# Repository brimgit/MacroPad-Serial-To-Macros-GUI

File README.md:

# MacroPad

A full-featured desktop app for controlling a custom ESP32-based macropad over serial. Built with a **React + Vite** frontend running inside a **pywebview** frameless window, backed by a pure-Python layer for serial communication, audio control, and macro execution.

---

## Features

### Macros
- Assign **press** and **hold** actions to all 8 keys and 4 encoder buttons
- **Configurable hold duration** per key (100–3000 ms, default 500 ms)
- **Drag keys to swap** their assignments directly on the grid
- **Copy / Paste** macros between keys with one click
- **Undo** the last macro edit with a single button
- Supported macro types:

  | Type | Description |
  |---|---|
  | Keyboard Key | Any letter, number, or special key |
  | Media Control | Play/pause, next/prev track, volume up/down, mute |
  | Function Key | F1–F24 |
  | Modifier Key | Ctrl, Shift, Alt, Win, and combos (Ctrl+C, Alt+Tab, etc.) |
  | Type Text | Types a free-form string |
  | Launch | Opens a file, folder, application, or URL |
  | System | Lock screen, sleep, shutdown, or restart |
  | Mute App | Toggles mute for the encoder's assigned audio source |
  | Recorded | Records a full keyboard sequence and replays it with original timing |
  | Multi Action | Chains multiple macro steps into a single key press |

### Encoders
- Each of the 4 encoders independently controls a volume source:
  - **Any audio app** (Discord, Spotify, browsers, games, etc.)
  - **🔊 Master Volume** — system-wide output level
  - **🎤 Microphone** — default capture device input level
- Each app can only be assigned to **one encoder at a time** — assigning it elsewhere automatically clears the previous one
- **Offline indicator** — encoder card shows a yellow **● OFFLINE** badge if the assigned app is not currently running
- Encoder **button macros** (press + hold) assignable per encoder, same types as keys
- **Mute toggle**: pressing the encoder button mutes/unmutes the source
  - LED ring turns **solid red** while muted
  - Turning while muted **flashes red continuously**, then gives 3 final blinks to confirm still muted
  - Mute state is **read on connect** so the ring reflects reality immediately

### LED Ring
Each encoder card shows a live **10-LED ring preview** that mirrors the physical device:
- **Volume display** — LEDs fill proportional to current volume %, shown for 2 s after each turn
- **Idle animations**:

  | Effect | Description |
  |---|---|
  | Off | Strip turns off after timeout |
  | Breathe | All LEDs pulse in and out (smootherstep curve) |
  | Wave | Brightness ripples across the ring |
  | Rainbow | Hue band scrolls around the ring |
  | Chase | Bright spot bounces with fade trail |
  | Color Cycle | All LEDs drift through the full spectrum |
  | Sparkle | Random LEDs flash in the encoder's color |

- **LED modes** (color while active):
  - **Default** — green→red gradient tracking volume
  - **Solid** — single custom color
  - **Fade** — gradient between two custom colors

### Profiles
- **Create, rename, duplicate, and delete** named profiles
- Each profile stores: all key macros, encoder button macros, encoder app assignments, LED mode/colors/effects
- **Import / Export** profiles as `.json` files
- Profiles are stored as **individual files** (`Data/profiles/{name}.json`) — easy to back up, diff, and share
- **Auto profile switching** — configure a list of trigger apps per profile; the active profile switches automatically when that app comes into focus

### Settings
| Setting | Description |
|---|---|
| Serial Port & Baud Rate | Connect to the MacroPad over any COM port |
| LED Brightness | Global brightness (0–100%) sent to device on change |
| Enc LED Off | Idle timeout before encoder strip turns off (2 / 5 / 10 s) |
| Effect Speed | Animation frame rate: 5 ms (Ultra) → 50 ms (Light) |
| Export / Import Profile | Save or load the active profile as a `.json` file |
| Start with Windows | Adds MacroPad to the Windows startup registry key |

### Other
- **Device auto-detection** — on startup the app sends a `PING` to the configured port and looks for `MACROPAD_OK`; if the wrong port is saved it scans all available ports automatically and updates the setting
- **Frameless window** with a custom title bar — minimize, maximize, and close buttons blend into the app's colour scheme; the bar is draggable
- **Collapsible sidebar** — collapse to icon-only mode to save screen space; hover tooltips identify each page
- **Auto-reconnect** — if the device is unplugged the app reconnects automatically and restores all LED state
- **Test Mode** — shows all 8 key assignments with live flash highlighting and a scrolling event log when keys are pressed
- **Firmware Upload** — compile and flash `.ino` sketches directly from the app via Arduino CLI with a live log output
- **Update checker** — checks GitHub for a newer version on the Settings page

---

## Hardware

PCB designed in **KiCad** — schematic, board files, and Gerber files are in `PCB_files/`. Order directly from any PCB manufacturer with the Gerbers.

**ESP32** microcontroller with:
- 4× rotary encoders with push button (A/B/C/D)
- 8× mechanical keys (1–8)
- 4× NeoPixel LED strips (10 LEDs each, surrounding each encoder knob)

---

## Running from Source

### Requirements
- Python 3.10+
- Node.js 18+ (for building the frontend)

### Install dependencies

```bash
git clone https://github.com/brimgit/MacroPad-Serial-To-Macros-GUI
cd MacroPad-Serial-To-Macros-GUI

# Python dependencies
pip install -r requirements.txt

# Frontend dependencies
cd frontend
npm install
cd ..
```

### Development mode (hot-reload)

```bash
# Terminal 1 — Vite dev server
cd frontend
npm run dev

# Terminal 2 — Python backend (connects to Vite at localhost:5173)
python src/main_webview.py --dev
```

### Production mode (no Node.js needed at runtime)

```bash
# Build the frontend once
cd frontend
npm run build
cd ..

# Run the app
python src/main_webview.py
```

### Python dependencies

| Package | Purpose |
|---|---|
| pywebview | Native frameless window hosting the React frontend |
| pyserial | Serial communication with ESP32 |
| keyboard | Macro execution and keystroke recording |
| pycaw | Windows audio session / endpoint volume control |
| psutil | Process name lookup for auto profile switching |

### Frontend stack

| Package | Purpose |
|---|---|
| React 19 | UI framework |
| Vite | Build tool and dev server |

---

## Project Structure

```
src/
  main_webview.py      # Entry point — creates frameless pywebview window
  api.py               # Python API exposed to React via pywebview JS bridge
  macro_manager.py     # Macro storage, persistence, and execution
  profile_manager.py   # Profile CRUD, per-file JSON persistence
  serial_manager.py    # Serial connection, device identification, auto-reconnect
  volume_manager.py    # Per-app, master, and microphone volume control (pycaw)
  foreground_watcher.py# Polls foreground window for auto profile switching
  utils.py             # Path helpers for PyInstaller and data directory

frontend/
  src/
    App.jsx                     # Root component, state, event listeners
    components/
      Sidebar.jsx               # Navigation, profile management, theme toggle, collapse
      TitleBar.jsx              # Custom frameless title bar with window controls
      MacroModal.jsx            # Shared macro assignment modal (all types + Multi Action)
    pages/
      MacrosPage.jsx            # 2×4 key grid — drag/swap, copy/paste, undo
      EncodersPage.jsx          # Encoder cards with LED ring, volume, button macros
      SettingsPage.jsx          # Serial, brightness, LED, startup, import/export
      UploadPage.jsx            # Arduino CLI firmware upload with live log
      TestPage.jsx              # Live key-press display and event log

Data/
  profiles/            # One .json file per profile + _meta.json for active pointer
  settings_serial.json # Serial port, brightness, LED timeout, effect speed

PCB_files/             # KiCad schematic, board, and Gerber files
MacroPad_Arduino_Code/ # ESP32 firmware
```

---

## Firmware

The Arduino sketch is in `MacroPad_Arduino_Code/`. Upload it via the **Upload Firmware** page in the app (requires Arduino CLI) or via the Arduino IDE.

The firmware handles:
- Encoder tick detection → `E:{id}:{+/-}` serial output (0-indexed)
- Key press/release with hold-duration reporting → `KP:{key}:DOWN` / `KP:{key}:UP:{ms}`
- Device identification → responds to `PING` with `MACROPAD_OK`
- NeoPixel LED control: color modes, brightness, idle animations, effect speed, timeout
- Serial command protocol: `BRIGHT:`, `{n}:color(r,g,b)`, `{n}:colorfade(...)`, `EFFECT:{n}:{id}`, `ENC_TIMEOUT:`, `EFFECT_SPEED:`
- EEPROM persistence of LED color/mode settings across power cycles

---

## License

[MIT License](https://opensource.org/license/MIT)

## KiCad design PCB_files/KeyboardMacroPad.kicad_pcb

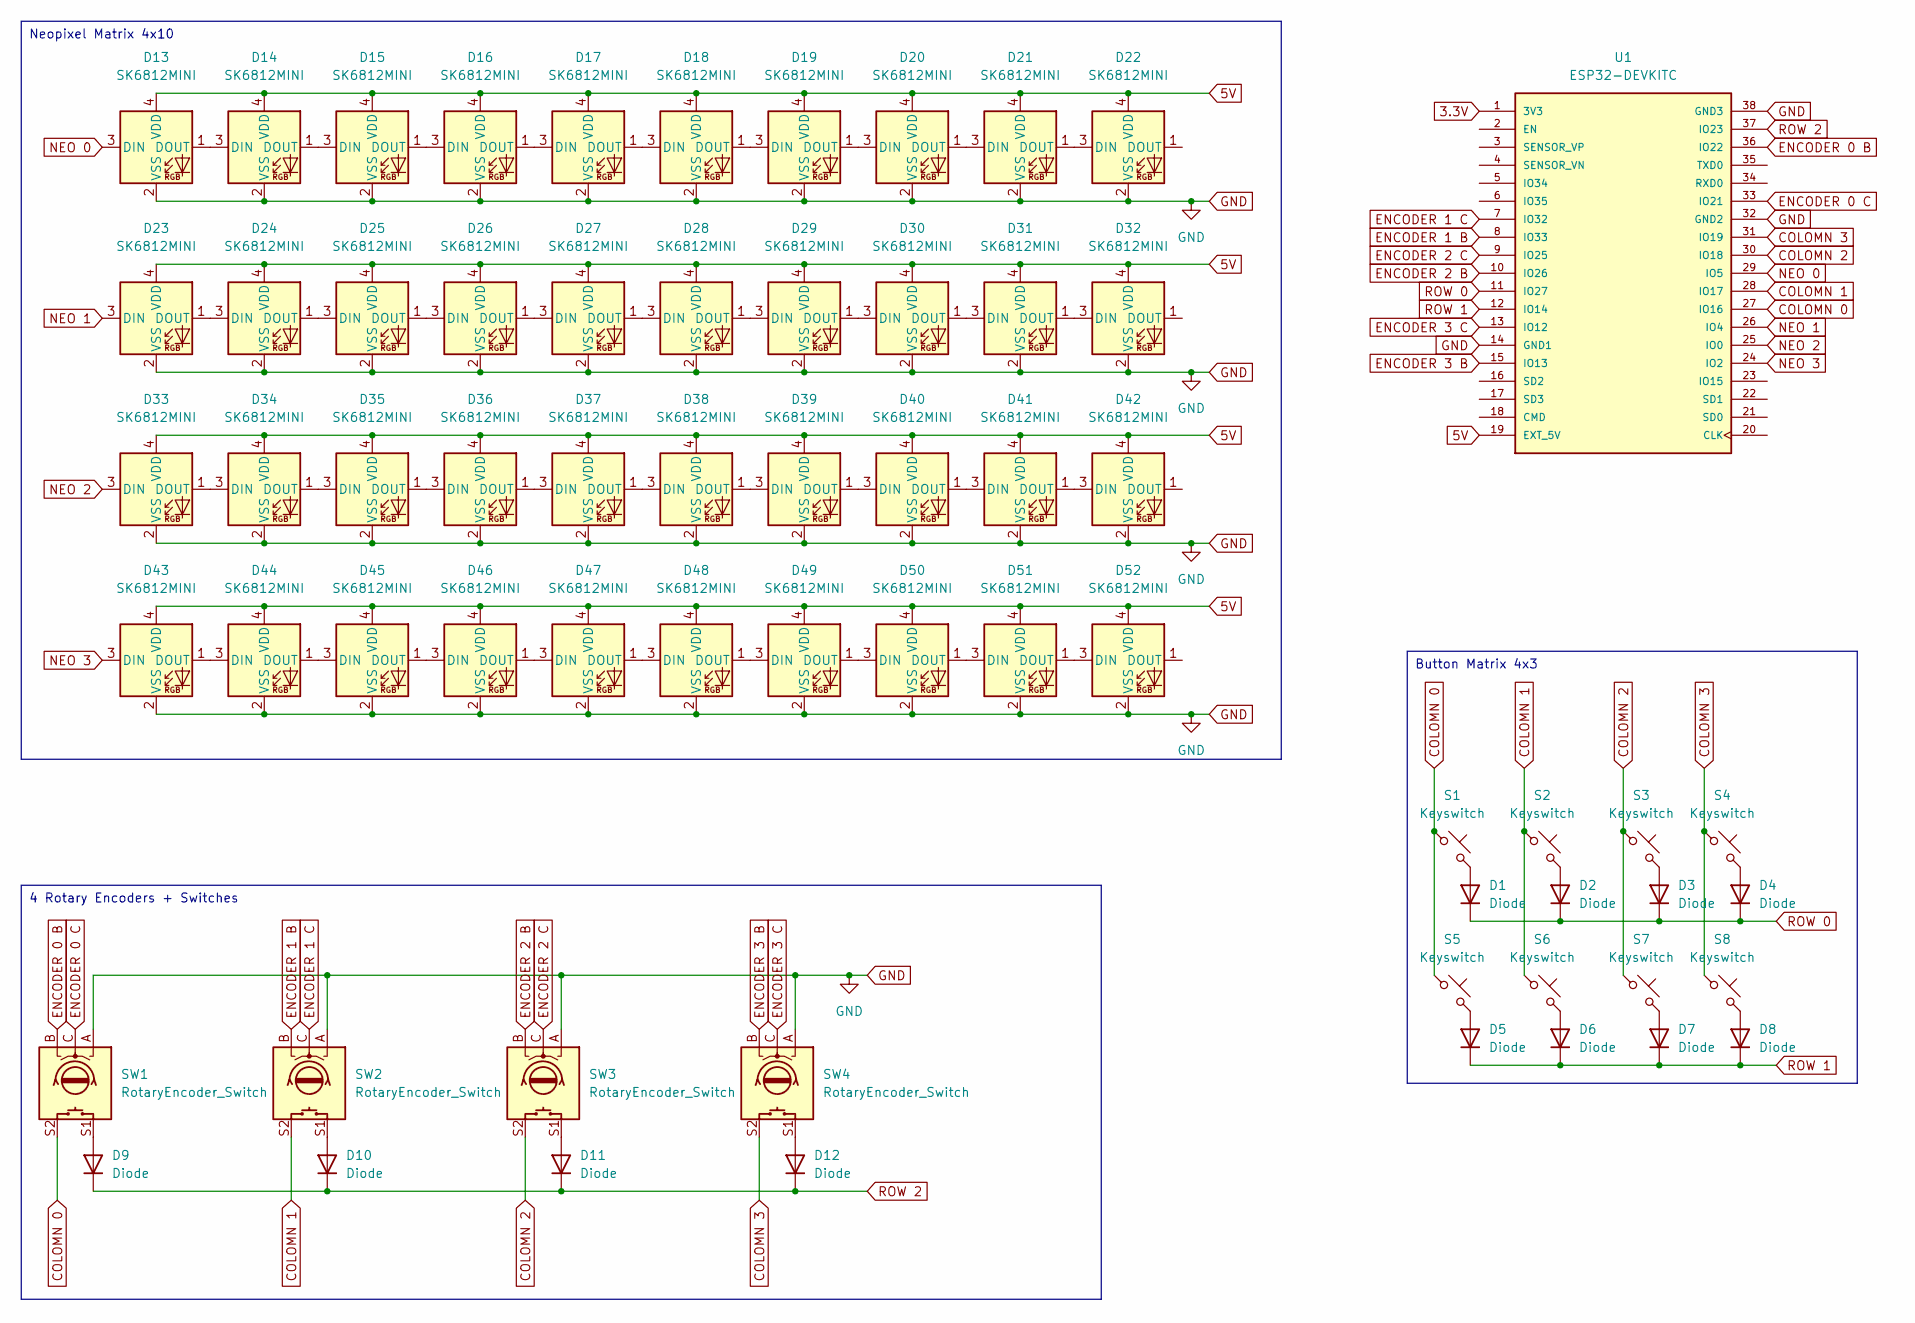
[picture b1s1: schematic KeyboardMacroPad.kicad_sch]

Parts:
D1, D2, D3, D4, D5, D6, D7, D8, D9, D10, D11, D12: Diode; Diode_SOD-123
D13, D14, D15, D16, D17, D18, D19, D20, D21, D22, D23, D24, D25, D26, D27, D28, D29, D30, D31, D32, D33, D34, D35, D36, D37, D38, D39, D40, D41, D42, D43, D44, D45, D46, D47, D48, D49, D50, D51, D52: SK6812MINI; LED_SK6812MINI_PLCC4_3.5x3.5mm_P1.75mm
S1, S2, S3, S4, S5, S6, S7, S8: Keyswitch; Hotswap_MX_1.00u
SW1, SW2, SW3, SW4: RotaryEncoder_Switch; RotaryEncoder_Alps_EC11E-Switch_Vertical_H20mm_CircularMoun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
U1: ESP32-DEVKITC; MODULE_ESP32-DEVKITC; PARTREV N/A

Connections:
3.3V: U1.1 (3V3)
5V: D13.4 (VDD), D14.4 (VDD), D15.4 (VDD), D16.4 (VDD), D17.4 (VDD), D18.4 (VDD), D19.4 (VDD), D20.4 (VDD), D21.4 (VDD), D22.4 (VDD), D23.4 (VDD), D24.4 (VDD), D25.4 (VDD), D26.4 (VDD), D27.4 (VDD), D28.4 (VDD), D29.4 (VDD), D30.4 (VDD), D31.4 (VDD), D32.4 (VDD), D33.4 (VDD), D34.4 (VDD), D35.4 (VDD), D36.4 (VDD), D37.4 (VDD), D38.4 (VDD), D39.4 (VDD), D40.4 (VDD), D41.4 (VDD), D42.4 (VDD), D43.4 (VDD), D44.4 (VDD), D45.4 (VDD), D46.4 (VDD), D47.4 (VDD), D48.4 (VDD), D49.4 (VDD), D50.4 (VDD), D51.4 (VDD), D52.4 (VDD), U1.19 (EXT_5V)
COLOMN 0: S1.1, S5.1, SW1.S2, U1.27 (IO16)
COLOMN 1: S2.1, S6.1, SW2.S2, U1.28 (IO17)
COLOMN 2: S3.1, S7.1, SW3.S2, U1.30 (IO18)
COLOMN 3: S4.1, S8.1, SW4.S2, U1.31 (IO19)
ENCODER 0 B: SW1.B, U1.36 (IO22)
ENCODER 0 C: SW1.C, U1.33 (IO21)
ENCODER 1 B: SW2.B, U1.8 (IO33)
ENCODER 1 C: SW2.C, U1.7 (IO32)
ENCODER 2 B: SW3.B, U1.10 (IO26)
ENCODER 2 C: SW3.C, U1.9 (IO25)
ENCODER 3 B: SW4.B, U1.15 (IO13)
ENCODER 3 C: SW4.C, U1.13 (IO12)
GND: D13.2 (VSS), D14.2 (VSS), D15.2 (VSS), D16.2 (VSS), D17.2 (VSS), D18.2 (VSS), D19.2 (VSS), D20.2 (VSS), D21.2 (VSS), D22.2 (VSS), D23.2 (VSS), D24.2 (VSS), D25.2 (VSS), D26.2 (VSS), D27.2 (VSS), D28.2 (VSS), D29.2 (VSS), D30.2 (VSS), D31.2 (VSS), D32.2 (VSS), D33.2 (VSS), D34.2 (VSS), D35.2 (VSS), D36.2 (VSS), D37.2 (VSS), D38.2 (VSS), D39.2 (VSS), D40.2 (VSS), D41.2 (VSS), D42.2 (VSS), D43.2 (VSS), D44.2 (VSS), D45.2 (VSS), D46.2 (VSS), D47.2 (VSS), D48.2 (VSS), D49.2 (VSS), D50.2 (VSS), D51.2 (VSS), D52.2 (VSS), SW1.A, SW2.A, SW3.A, SW4.A, U1.14 (GND1), U1.32 (GND2), U1.38 (GND3)
NEO 0: D13.3 (DIN), U1.29 (IO5)
NEO 1: D23.3 (DIN), U1.26 (IO4)
NEO 2: D33.3 (DIN), U1.25 (IO0)
NEO 3: D43.3 (DIN), U1.24 (IO2)
unnamed: D1.2 (A), S1.2
unnamed: D2.2 (A), S2.2
unnamed: D3.2 (A), S3.2
unnamed: D4.2 (A), S4.2
unnamed: D5.2 (A), S5.2
unnamed: D6.2 (A), S6.2
unnamed: D7.2 (A), S7.2
unnamed: D8.2 (A), S8.2
unnamed: D9.2 (A), SW1.S1
unnamed: D10.2 (A), SW2.S1
unnamed: D11.2 (A), SW3.S1
unnamed: D12.2 (A), SW4.S1
unnamed: D13.1 (DOUT), D14.3 (DIN)
unnamed: D14.1 (DOUT), D15.3 (DIN)
unnamed: D15.1 (DOUT), D16.3 (DIN)
unnamed: D16.1 (DOUT), D17.3 (DIN)
unnamed: D17.1 (DOUT), D18.3 (DIN)
unnamed: D18.1 (DOUT), D19.3 (DIN)
unnamed: D19.1 (DOUT), D20.3 (DIN)
unnamed: D20.1 (DOUT), D21.3 (DIN)
unnamed: D21.1 (DOUT), D22.3 (DIN)
unnamed: D23.1 (DOUT), D24.3 (DIN)
unnamed: D24.1 (DOUT), D25.3 (DIN)
unnamed: D25.1 (DOUT), D26.3 (DIN)
unnamed: D26.1 (DOUT), D27.3 (DIN)
unnamed: D27.1 (DOUT), D28.3 (DIN)
unnamed: D28.1 (DOUT), D29.3 (DIN)
unnamed: D29.1 (DOUT), D30.3 (DIN)
unnamed: D30.1 (DOUT), D31.3 (DIN)
unnamed: D31.1 (DOUT), D32.3 (DIN)
unnamed: D33.1 (DOUT), D34.3 (DIN)
unnamed: D34.1 (DOUT), D35.3 (DIN)
unnamed: D35.1 (DOUT), D36.3 (DIN)
unnamed: D36.1 (DOUT), D37.3 (DIN)
unnamed: D37.1 (DOUT), D38.3 (DIN)
unnamed: D38.1 (DOUT), D39.3 (DIN)
unnamed: D39.1 (DOUT), D40.3 (DIN)
unnamed: D40.1 (DOUT), D41.3 (DIN)
unnamed: D41.1 (DOUT), D42.3 (DIN)
unnamed: D43.1 (DOUT), D44.3 (DIN)
unnamed: D44.1 (DOUT), D45.3 (DIN)
unnamed: D45.1 (DOUT), D46.3 (DIN)
unnamed: D46.1 (DOUT), D47.3 (DIN)
unnamed: D47.1 (DOUT), D48.3 (DIN)
unnamed: D48.1 (DOUT), D49.3 (DIN)
unnamed: D49.1 (DOUT), D50.3 (DIN)
unnamed: D50.1 (DOUT), D51.3 (DIN)
unnamed: D51.1 (DOUT), D52.3 (DIN)
ROW 0: D1.1 (K), D2.1 (K), D3.1 (K), D4.1 (K), U1.11 (IO27)
ROW 1: D5.1 (K), D6.1 (K), D7.1 (K), D8.1 (K), U1.12 (IO14)
ROW 2: D9.1 (K), D10.1 (K), D11.1 (K), D12.1 (K), U1.37 (IO23)

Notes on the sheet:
Neopixel Matrix 4x10
4 Rotary Encoders + Switches
Button Matrix 4x3

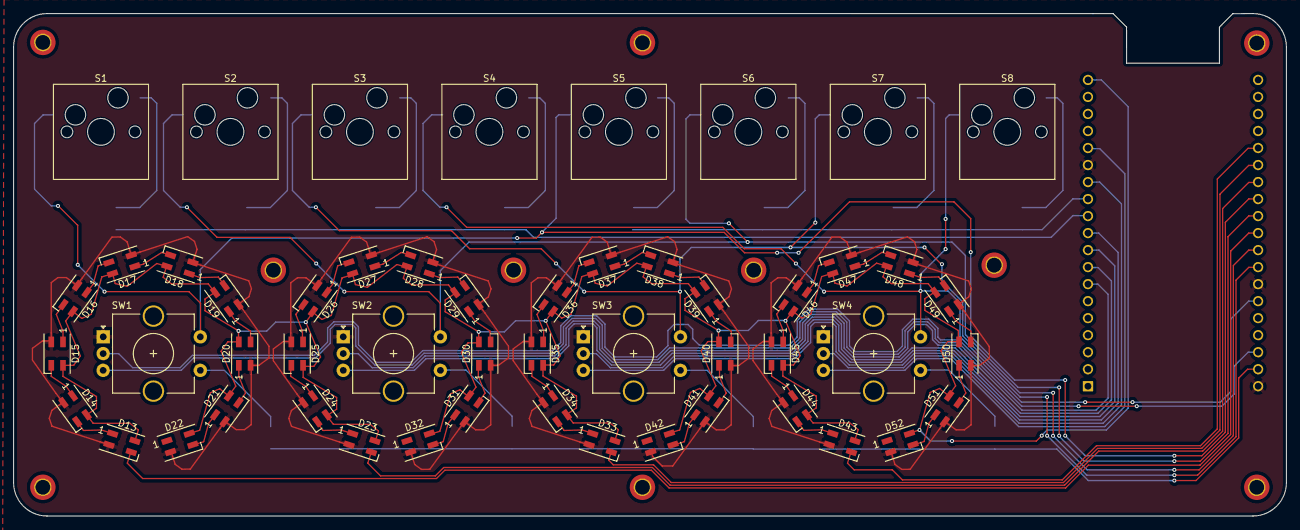
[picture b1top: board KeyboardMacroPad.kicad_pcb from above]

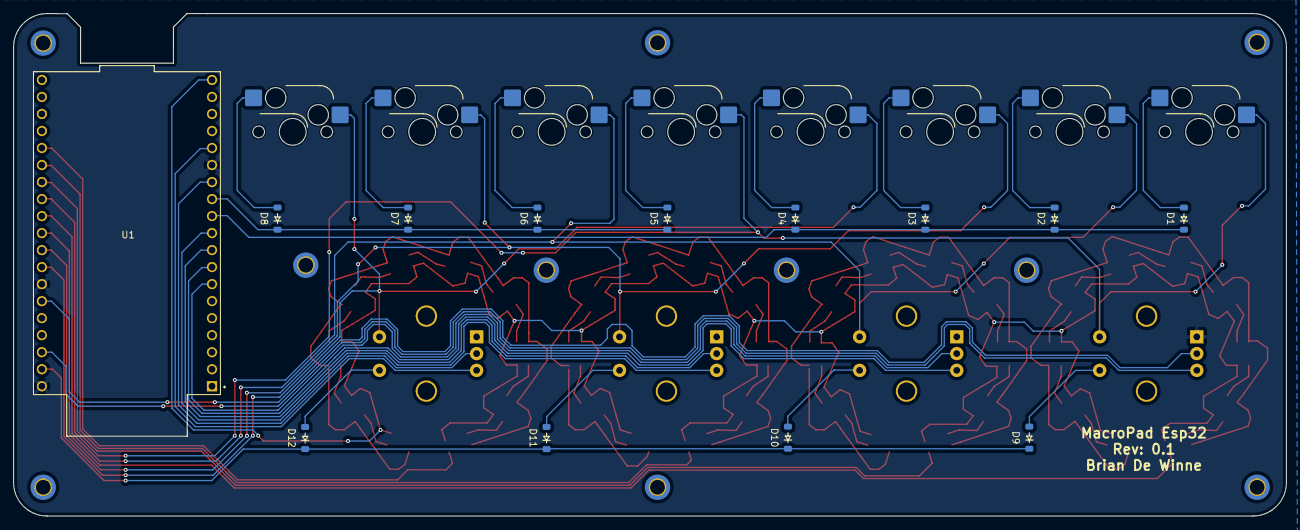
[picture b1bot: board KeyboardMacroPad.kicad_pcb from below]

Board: 2 copper layers, 190.0 x 75.0 mm, 65 parts (13 on the bottom side), 69 nets.

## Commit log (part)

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2024-04-22 Start GUI - Serial Com, Remove/Add Macro, Show Serial Data
2024-04-22 New Model file, added qt Designer files for GUI desgin, fixed not assigning macro to correct command.
2024-04-22 Fixed removing macros already assigned in the macros.json file. Added settings menu to change COM port and Baud rate. Added logging and exception handling
2024-04-22 Fixed executing Macro. now when inputting a macro for given serial data received. when re sending serial data, macro that is specified in macros.json file will be executed
2024-04-22 added the option to pick between funtion keys, keyboard inputs, media control keys and modifier keys, Fixed remove function
2024-04-22 removed redundant text input box
2024-04-22 added keyboard library, functionality of media control buttons work now
2024-04-22 remove redundant buttons, refresh macro button and save button, this now happens when set/edit button is pressed
2024-04-22 Made Gui look modern flat, with retractable side menu and logo added, Sidebar needs to be fixed when retracted cant open it back up again
2024-04-23 fixed sidebar padding, removed the docking option of sidebar, removed QT Designer files. Change library from pyautogui to keyboard.
2024-04-23 Added ErrorHandling and possibility for log files to be created when error occur
2024-04-23 refactored the code, removed unused librarys, added minimize to tray with icon added
2024-04-23 test commit
2024-04-23 Added a .ico changed references to folders, made an installer
2024-04-23 added Arduino code and README file
2024-04-23 readme changes
2024-04-23 readme file changes
2024-04-23 added requirements.txt fo all the required dependencies
2024-04-23 referred to requirements.txt in readme
2024-04-27 changed folder name to BrimPad in the appdata where macros.json is being saved
2024-04-27 added .gitignore, fixed stop media control function.
2024-04-27 added more to gitignore
2024-04-27 added ignore to startup data being send, added so you can't assign a macro to nothing with fitting error code
2024-04-27 no you can select the com port when the app starts up
2024-04-27 added settings.json where the default com port and baud rate is stored + implemented in gui.py for saving and loading said settings
2024-04-27 added device description to com port selection for ease of identification
2024-04-27 changed settings file name for serial connecion, from settings.json -> settings_serial.json
2024-04-28 added support to control seperate application volume with the encoder, this is currently specified in the gui.py
2024-04-28 changed apps to control with encoder
2024-04-29 added refresh button to settings window
2024-05-07 changed max brightness led's in arduino code
2024-05-22 added support to change led color's
2024-05-22 stores set colots in the EEPROM for when reloading color stays the same
2024-05-22 if no data on EEPROM, default color is white
2024-05-23 Colortransition or static color options added to code
2024-05-23 added 3 modes, static color, fade from color to color and set colorchange at a percentage by using the complementary color of the color entered
2024-05-29 changed adafruit library to fastled library due to bugs
2024-05-29 added upload button to update the esp32 firmware
2024-06-05 added gui funtion to change led color and update led strip to correct percentage. baud rate is now 500000
2024-06-05 Changes to pycaw for audio handling and added dropdown to select wich encoder controls what program's audio, selecion is made from available audio sources seen in volume mixer
2024-06-05 fixed issues with volume changes
2024-06-06 Moved the VolumeManager class to this new file. Imported the VolumeManager from volume_manager.py.
2024-06-06 bug fixes
2024-06-09 added KiCad pcb and schematics + gerber files
2024-06-09 changes to README
2026-05-31 Add launcher, theme/widgets modules, fix gitignore, update deps
2026-05-31 Add profiles, idle effects, mute LEDs, system tray, test mode, auto-switch, and more
2026-05-31 Update README with full feature documentation
